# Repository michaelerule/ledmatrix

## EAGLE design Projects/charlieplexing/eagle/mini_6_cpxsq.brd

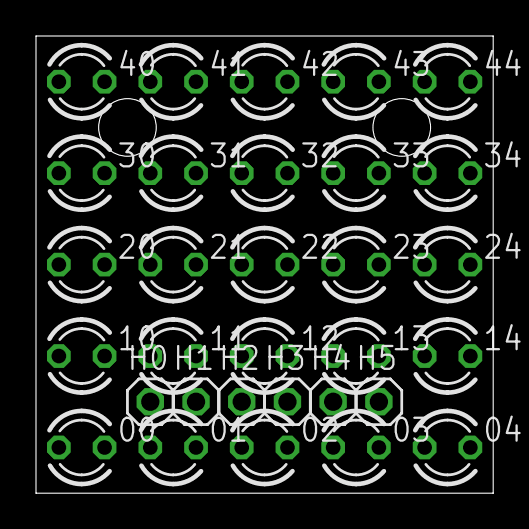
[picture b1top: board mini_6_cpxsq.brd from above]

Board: 2 copper layers, 25.4 x 25.4 mm, 31 parts (0 on the bottom side), 6 nets, no tracks yet.

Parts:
00, 01, 02, 03, 04, 10, 11, 12, 13, 14, 20, 21, 22, 23, 24, 30, 31, 32, 33, 34, 40, 41, 42, 43, 44: LED3MM
H0, H1, H2, H3, H4, H5: 1X01

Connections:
D: 00.A, 11.A, 22.A, 33.A, 44.A, H5.1
S0: 00.K, 01.A, 02.A, 03.A, 04.A, 10.K, 20.K, 30.K, 40.K, H0.1
S1: 01.K, 10.A, 11.K, 12.A, 13.A, 14.A, 21.K, 31.K, 41.K, H1.1
S2: 02.K, 12.K, 20.A, 21.A, 22.K, 23.A, 24.A, 32.K, 42.K, H2.1
S3: 03.K, 13.K, 23.K, 30.A, 31.A, 32.A, 33.K, 34.A, 43.K, H3.1
S4: 04.K, 14.K, 24.K, 34.K, 40.A, 41.A, 42.A, 43.A, 44.K, H4.1

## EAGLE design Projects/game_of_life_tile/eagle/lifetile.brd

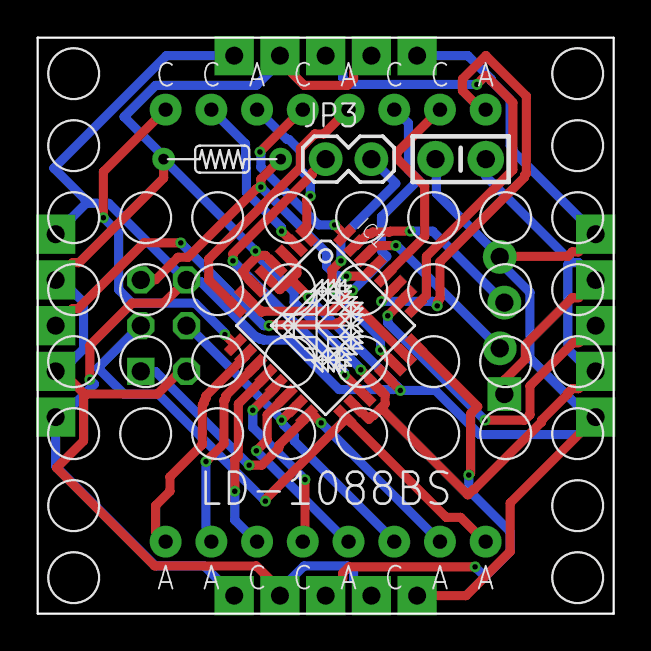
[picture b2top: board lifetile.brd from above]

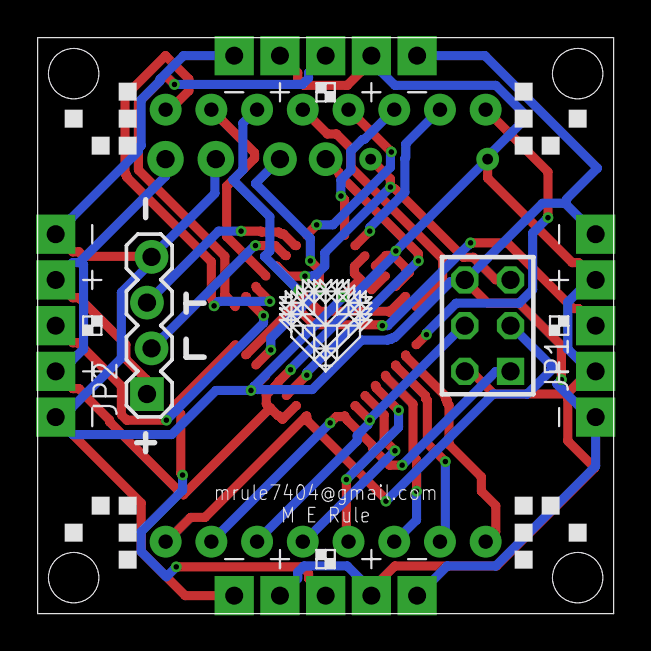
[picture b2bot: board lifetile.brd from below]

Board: 2 copper layers, 32.0 x 32.0 mm, 13 parts (7 on the bottom side), 27 nets.

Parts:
C3: CAP-PTH-SMALL-KIT
IC1: MEGA8-AI; TQFP32-08
JP1: AVR-ISP-6
JP2: 1X04_LOCK
JP3: 1X02
U$1: LD-1088BS
U$2: R-7
U$3, U$7: LOGO
U$4, U$5, U$6, U$11: EDGE_5_PTH; EDGE_5_SMT_PTH

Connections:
GND: C3.2, IC1.3, IC1.5, IC1.21, JP1.6, JP2.4, U$4.G1, U$4.G2, U$5.G1, U$5.G2, U$6.G1, U$6.G2, U$11.G1, U$11.G2
unnamed: IC1.17, JP1.3, U$1.A4
unnamed: IC1.16, JP1.1, U$1.A5
unnamed: IC1.15, JP1.4, U$1.C6
unnamed: IC1.14, U$1.A6
unnamed: IC1.13, U$1.C7
unnamed: IC1.12, U$1.C8
unnamed: IC1.11, U$1.A7
unnamed: IC1.10, U$1.A8
unnamed: IC1.29, JP1.5, U$2.P$2
unnamed: IC1.9, U$1.C5
unnamed: IC1.2, U$1.C4
unnamed: IC1.1, U$1.A3
unnamed: IC1.32, U$1.C3
unnamed: IC1.8, U$1.A2
unnamed: IC1.7, U$1.C2
unnamed: IC1.28, U$1.C1
unnamed: IC1.27, U$1.A1
unnamed: IC1.26, U$4.D
unnamed: IC1.30, JP2.2
unnamed: IC1.23, U$11.D
unnamed: IC1.31, JP2.3
unnamed: IC1.19, JP3.1
unnamed: IC1.22, JP3.2
unnamed: IC1.25, U$5.D
unnamed: IC1.24, U$6.D
VCC: C3.1, IC1.4, IC1.6, IC1.18, IC1.20, JP1.2, JP2.1, U$2.P$1, U$4.V1, U$4.V2, U$5.V1, U$5.V2, U$6.V1, U$6.V2, U$11.V1, U$11.V2

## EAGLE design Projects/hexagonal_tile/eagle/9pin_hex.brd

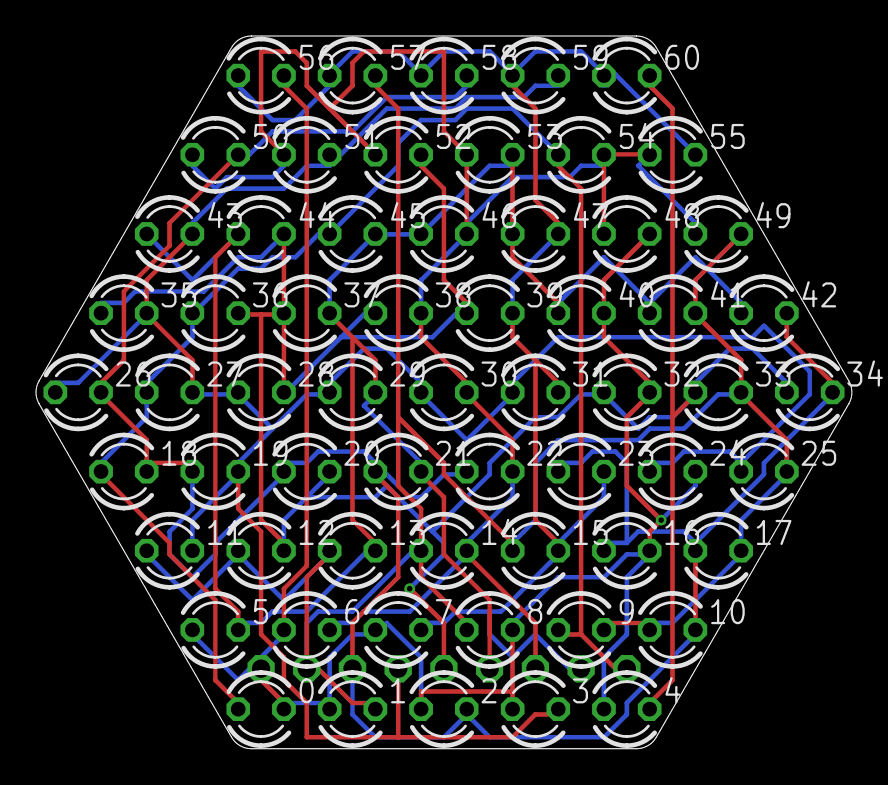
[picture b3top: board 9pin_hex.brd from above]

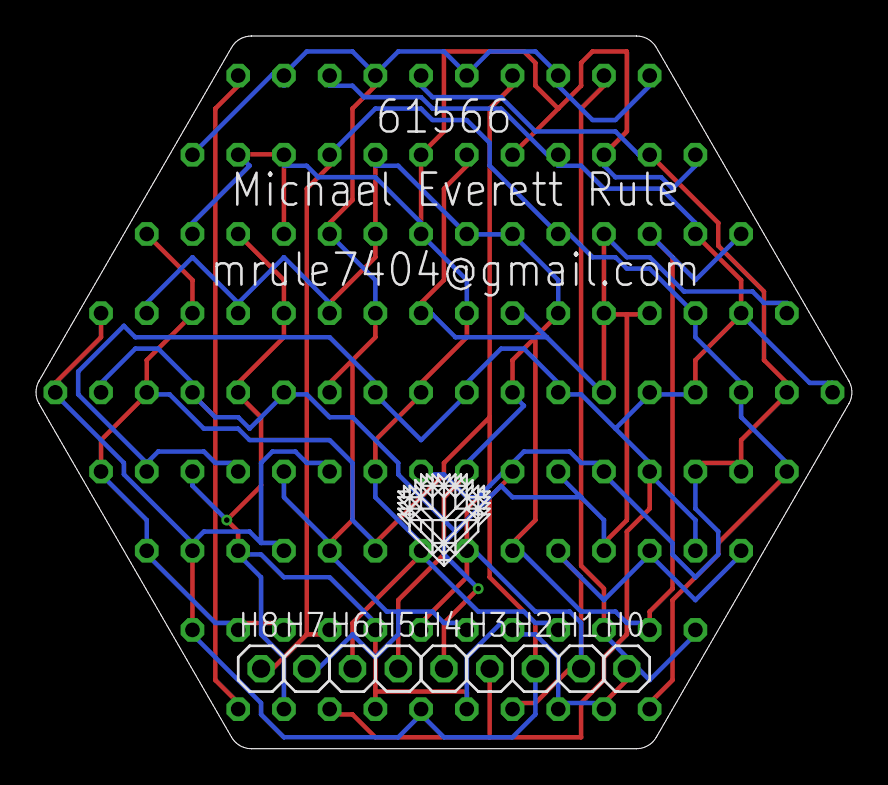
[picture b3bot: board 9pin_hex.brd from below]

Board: 2 copper layers, 45.3 x 39.6 mm, 71 parts (10 on the bottom side), 9 nets.

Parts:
0, 1, 2, 3, 4, 5, 6, 7, 8, 9, 10, 11, 12, 13, 14, 15, 16, 17, 18, 19, 20, 21, 22, 23, 24, 25, 26, 27, 28, 29, 30, 31, 32, 33, 34, 35, 36, 37, 38, 39, 40, 41, 42, 43, 44, 45, 46, 47, 48, 49, 50, 51, 52, 53, 54, 55, 56, 57, 58, 59, 60: LED3MM
H0, H1, H2, H3, H4, H5, H6, H7, H8: 1X01
H9: LOGO

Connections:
S0: 0.K, 1.A, 2.A, 3.A, 4.A, 5.A, 6.A, 7.A, 8.K, 16.K, 24.K, 32.K, 40.K, 48.K, 56.K, H0.1
S1: 1.K, 8.A, 9.K, 10.A, 11.A, 12.A, 13.A, 14.A, 15.A, 17.K, 25.K, 33.K, 41.K, 49.K, 57.K, H1.1
S2: 2.K, 10.K, 16.A, 17.A, 18.K, 19.A, 20.A, 21.A, 22.A, 23.A, 26.K, 34.K, 42.K, 50.K, 58.K, H2.1
S3: 3.K, 11.K, 19.K, 24.A, 25.A, 26.A, 27.K, 28.A, 29.A, 30.A, 31.A, 35.K, 43.K, 51.K, 59.K, H3.1
S4: 4.K, 12.K, 20.K, 28.K, 32.A, 33.A, 34.A, 35.A, 36.K, 37.A, 38.A, 39.A, 44.K, 52.K, 60.K, H4.1
S5: 5.K, 13.K, 21.K, 29.K, 37.K, 40.A, 41.A, 42.A, 43.A, 44.A, 45.K, 46.A, 47.A, 53.K, H5.1
S6: 6.K, 14.K, 22.K, 30.K, 38.K, 46.K, 48.A, 49.A, 50.A, 51.A, 52.A, 53.A, 54.K, 55.A, H6.1
S7: 7.K, 15.K, 23.K, 31.K, 39.K, 47.K, 55.K, 56.A, 57.A, 58.A, 59.A, 60.A, H7.1
S8: 0.A, 9.A, 18.A, 27.A, 36.A, 45.A, 54.A, H8.1

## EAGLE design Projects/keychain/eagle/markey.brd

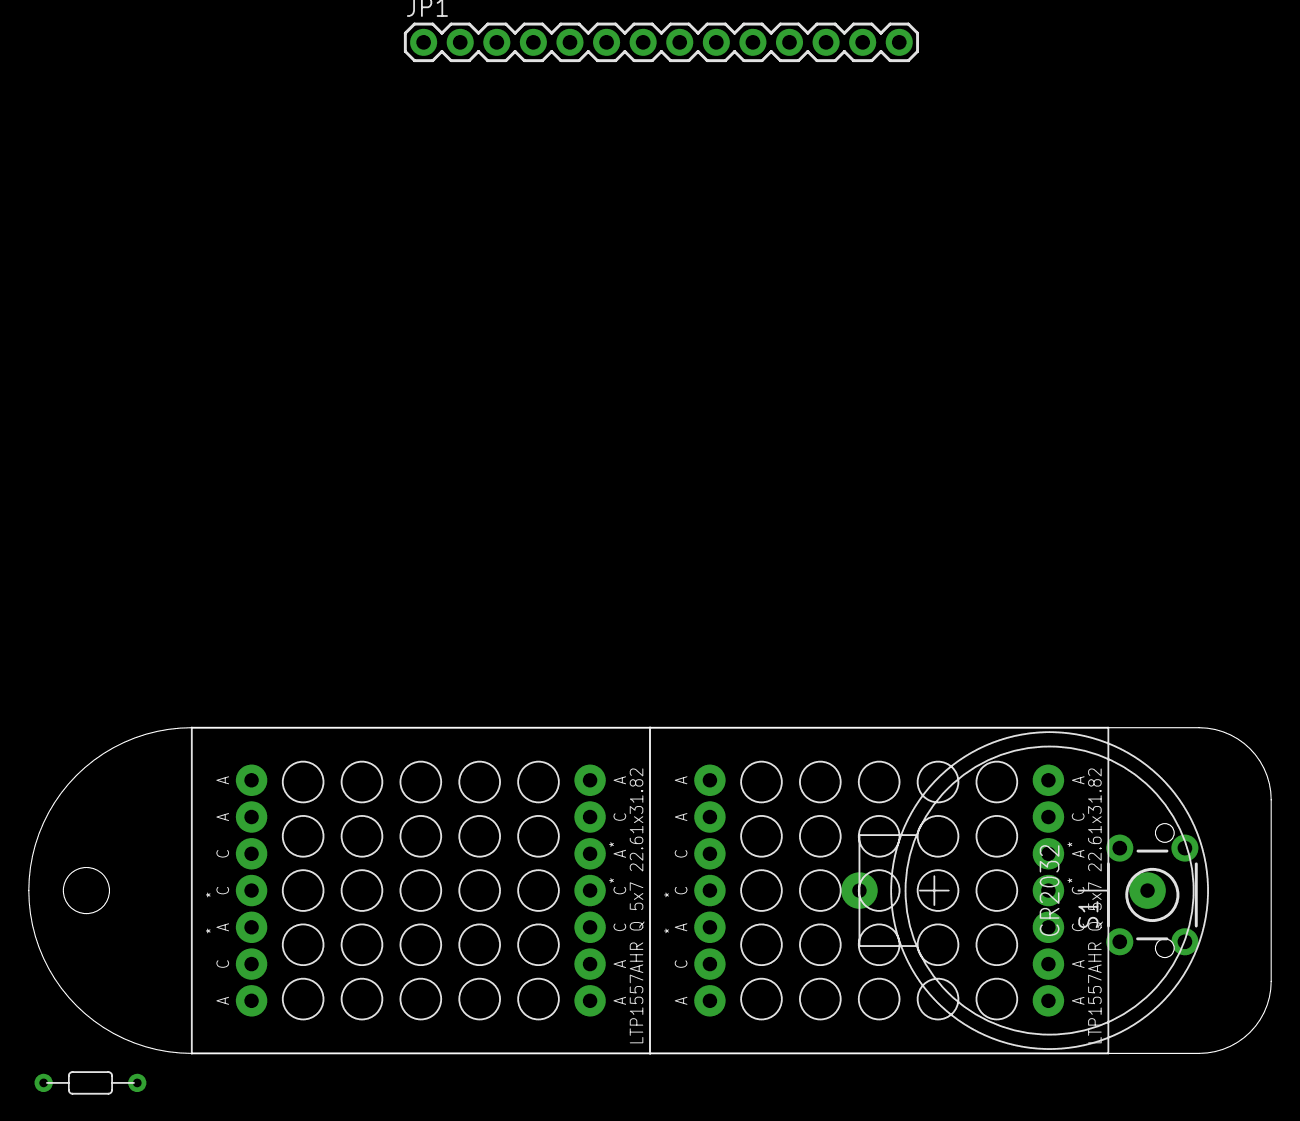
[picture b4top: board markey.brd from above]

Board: 2 copper layers, 86.2 x 22.6 mm, 7 parts (1 on the bottom side), 17 nets, no tracks yet.

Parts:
IC1: MEGA8-AI; TQFP32-08
JP1: M14; 1X14
S1: TACTILE-PTH
U$1, U$2: 5X7_SMALL_MX; 5X7
U$3: R-7
U$4: CR2032; CR2032_EBAY

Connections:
GND: IC1.3, IC1.5, IC1.21, U$4.P$2
unnamed: IC1.27, JP1.10, U$1.P$9, U$2.P$5, U$2.P$10
unnamed: IC1.28, JP1.9, U$1.P$4, U$1.P$11, U$2.P$2
unnamed: IC1.12, JP1.2, U$1.P$2, U$2.P$4, U$2.P$11
unnamed: IC1.11, JP1.3, U$1.P$5, U$1.P$10, U$2.P$9
unnamed: IC1.13, JP1.1, U$1.P$1, U$2.P$3
unnamed: IC1.10, JP1.4, U$1.P$7, U$2.P$6
unnamed: IC1.9, JP1.5, U$1.P$8, U$2.P$12
unnamed: IC1.32, JP1.8, U$1.P$3, U$2.P$1
unnamed: IC1.26, JP1.11, U$1.P$6, U$2.P$7
unnamed: IC1.25, JP1.12, U$1.P$12, U$2.P$8
unnamed: IC1.23, JP1.14, U$2.P$14
unnamed: IC1.24, JP1.13, U$2.P$13
unnamed: IC1.1, JP1.7, U$1.P$14
unnamed: IC1.2, JP1.6, U$1.P$13
unnamed: IC1.29, U$3.P$2
VCC: IC1.4, IC1.6, IC1.18, IC1.20, U$3.P$1, U$4.P$1

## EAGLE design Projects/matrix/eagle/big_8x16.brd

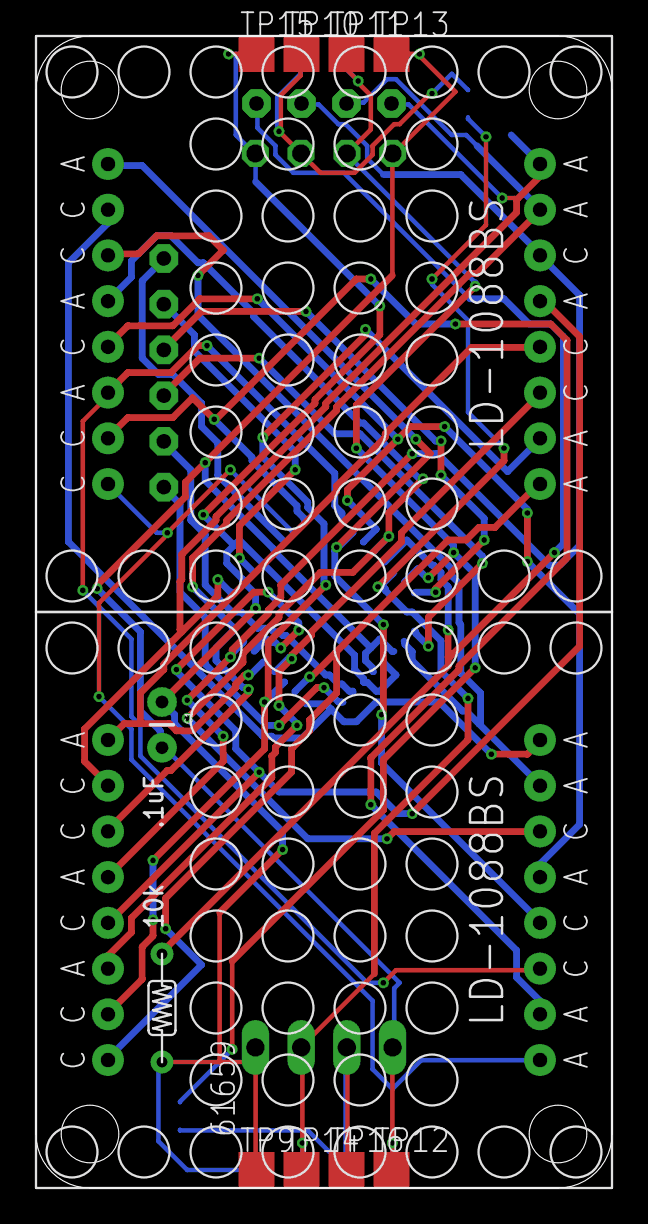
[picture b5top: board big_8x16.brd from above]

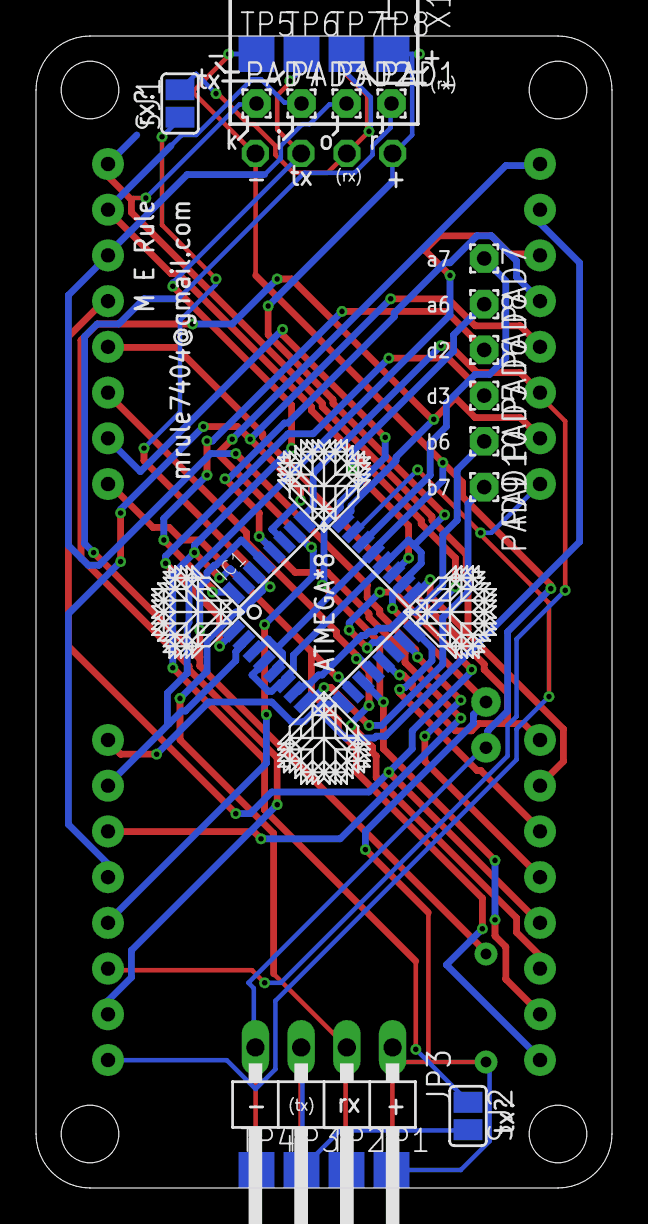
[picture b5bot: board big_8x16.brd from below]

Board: 2 copper layers, 32.0 x 64.0 mm, 39 parts (27 on the bottom side), 29 nets.

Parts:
C1: CAP-PTH-SMALL
IC1: MEGA8-AI; TQFP32-08
JP3: 1X04/90
PAD1, PAD2, PAD3, PAD4, PAD5, PAD6, PAD7, PAD8, PAD9, PAD10: 1,6/0,8
SJ1, SJ2: SJ
TP1, TP2, TP3, TP4, TP5, TP6, TP7, TP8, TP9, TP10, TP11, TP12, TP13, TP14, TP15, TP16: TPSQTP20SQ; TP20SQ
U$1, U$2: LD-1088BS
U$3: R-6
U$5, U$6, U$7, U$8: LOGO
X1: SSW-104-02-S-S-RA

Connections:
unnamed: IC1.24, U$1.A7, U$2.C4
unnamed: IC1.25, U$1.C8, U$2.A3
unnamed: IC1.26, U$1.C7, U$2.A1
unnamed: IC1.27, U$1.A6, U$2.C3
unnamed: IC1.28, U$1.C6, U$2.A2
unnamed: IC1.2, U$1.A5, U$2.C2
unnamed: IC1.9, U$1.A4, U$2.C1
unnamed: IC1.15, PAD2.1, U$1.A2, U$2.C6
unnamed: IC1.14, U$1.C3, U$2.A6
unnamed: IC1.13, U$1.A1, U$2.C7
unnamed: IC1.12, U$1.A3, U$2.C8
unnamed: IC1.11, U$1.C4, U$2.A7
unnamed: IC1.10, U$1.C5, U$2.A8
unnamed: IC1.16, PAD3.1, U$1.C2, U$2.A5
unnamed: IC1.17, PAD4.1, U$1.C1, U$2.A4
unnamed: IC1.1, PAD5.1
unnamed: IC1.23, U$1.A8, U$2.C5
unnamed: C1.2, IC1.3, IC1.5, IC1.21, JP3.4, TP4.TP, TP5.TP, TP12.TP, TP13.TP, X1.4
unnamed: C1.1, IC1.4, IC1.6, IC1.18, IC1.20, JP3.1, TP1.TP, TP8.TP, TP9.TP, TP15.TP, U$3.P$2, X1.1
unnamed: IC1.32, PAD6.1
unnamed: SJ1.2, TP7.TP, TP10.TP, X1.2
unnamed: JP3.3, SJ2.2, TP3.TP, TP16.TP
unnamed: IC1.31, SJ2.1, TP6.TP, TP11.TP, X1.3
unnamed: IC1.30, JP3.2, SJ1.1, TP2.TP, TP14.TP
unnamed: IC1.29, PAD1.1, U$3.P$1
unnamed: IC1.22, PAD7.1
unnamed: IC1.19, PAD8.1
unnamed: IC1.8, PAD9.1
unnamed: IC1.7, PAD10.1

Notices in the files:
parts and their libraries:
SparkFun-Capacitors: Licensing: CC v3.0 Share-Alike You are welcome to use this library for commercial purposes.
